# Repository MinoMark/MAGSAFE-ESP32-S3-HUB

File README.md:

# MAGSAFE ESP32-S3 HUB
**Don't get up, just use this...**

## About My Project

What is my project? My project is one of a kind! I am using an ESP32-S3 microcontroller chip to power a smart 2.8" TFT touchscreen. As mentioned in the title, it is listed as being MagSafe compatible, which is ingenious, right? Who does not want to have it charging 24/7? Or maybe not? Well, that has been solved too! I have added a 3.7V 5000mAh LiPo battery that can last well over 24 hours. But that is not all! I have also included an audio amplifier with a super loud and crisp speaker so you can hear those alerts and alarms from meters away.

I’ve made this project because I am tired of opening my laptop just to have a look at the time, set a timer, turn on smart lights, or do almost anything else. With my design, I’ll be able to control these all in one. You can have it play soothing music or play annoying alarms whenever.

**How to use:**

Plug it into the dedicated USB-C port at the bottom side with a USB-C cable or any compatible iPhone MagSafe charger. Let it charge for 10 minutes to an hour to fully charge. For MagSafe, let it charge for 30 minutes to an hour and 15 minutes.

**Wiring Diagram:**

The wiring diagram for POWER:

The wiring diagram for AUDIO:

## Schematics
The schematics of my final design, what I'll be using to make the main PCB.

## PCB
The fully routed PCB, with fun easter egg and smart eletrical wiring choices that save money and change the path of electricity more efficiently.

## CAD
A full design of the parts.

## BOM

# Bill of Materials

| Part | Type | Quantity | Unit price (USD) | Line total (USD) | Link | Vendor | Funding | Notes | Reference | Footprint | Datasheet | MPN | LCSC |
|---|---|---|---|---|---|---|---|---|---|---|---|---|---|
| Shipping (JLCONE) | Shipping | 1 | 12.51 | 12.51 | [Link](<https://jlcpcb.com/?from=VGS&utm_source=google&utm_medium=cpc&utm_campaign=14177189905&gad_source=1&gad_campaignid=14177189905&gbraid=0AAAAABS1QqkgPoFOHUy_26J4N5kBx4Aa3&gclid=Cj0KCQiAwdDXBhDuARIsAFdLukmN-B7r3FdQKI8Ma6WjcPEJgnZSJuI_80tu4TU9jCkDFhZ-cYRUD3oaAn0kEALw_wcB>) | JLCPCB | Grant |  | N/A | N/A | N/A | N/A | N/A |
| Shipping (AliExpress) | Shipping | 1 | 2.03 | 2.03 | N/A | AliExpress | Grant |  | N/A | N/A | N/A | N/A | N/A |
| Tax (AliExpress) | Tax or fee | 1 | 1.74 | 1.74 | N/A | AliExpress | Grant |  | N/A | N/A | N/A | N/A | N/A |
| MAX98357A audio amplifier | Part | 1 | 2.07 | 2.07 | [Link](<https://www.aliexpress.com/item/1005007003802663.html?spm=a2g0o.productlist.main.4.2bd23ce0doG6x8&aem_p4p_detail=202611050133081315319932123740002772996&algo_pvid=0ad6be40-46e3-4f00-9430-e9820924795f&algo_exp_id=0ad6be40-46e3-4f00-9430-e9820924795f-3&pdp_ext_f=%7B%22order%22%3A%223834%22%2C%22spu_best_type%22%3A%22price%22%2C%22eval%22%3A%221%22%2C%22fromPage%22%3A%22search%22%7D&pdp_npi=6%40dis%21AUD%212.99%212.84%21%21%2113.80%2113.11%21%402101ca9517938711880116699e0d41%2112000052658790894%21sea%21AU%212961347876%21X%211%210%21n_tag%3A-29919%3Bd%3A20f6a0d2%3Bm03_new_user%3A-29895%3BpisId%3A5000000220905999&curPageLogUid=gHNWoxg3Cup0&utparam-url=scene%3Asearch%7Cquery_from%3A%7Cx_object_id%3A1005007003802663%7C_p_origin_prod%3A&search_p4p_id=202611050133081315319932123740002772996_1>) | AliExpress | Grant |  | MAX98357A | N/A | [Datasheet](<https://www.analog.com/media/en/technical-documentation/data-sheets/MAX98357A-MAX98357B.pdf>) | N/A | N/A |
| Wireless charger receiver | Part | 1 | 2.92 | 2.92 | [Link](<https://www.aliexpress.com/item/1005006917890401.html?spm=a2g0o.productlist.main.21.5befc5e30wHdxF&algo_pvid=c3f727d4-7764-4de2-9cfe-4073aea75173&algo_exp_id=c3f727d4-7764-4de2-9cfe-4073aea75173-18&pdp_ext_f=%7B%22order%22%3A%22260%22%2C%22spu_best_type%22%3A%22price%22%2C%22eval%22%3A%221%22%2C%22fromPage%22%3A%22search%22%7D&pdp_npi=6%40dis%21AUD%213.98%213.49%21%21%212.75%212.41%21%402101d2e717938715347906588e0f1b%2112000038722150536%21sea%21AU%212961347876%21X%211%210%21n_tag%3A-29919%3Bd%3A20f6a0d2%3Bm03_new_user%3A-29895%3BpisId%3A5000000220770329&curPageLogUid=ptJgFovmIGzU&utparam-url=scene%3Asearch%7Cquery_from%3A%7Cx_object_id%3A1005006917890401%7C_p_origin_prod%3A>) | AliExpress | Grant |  | 5W | N/A | N/A | N/A | N/A |
| Battery management board | Part | 1 | 0.80 | 0.80 | [Link](<https://www.aliexpress.com/item/1005013472412754.html?spm=a2g0o.productlist.main.9.7fb4e999hY7Rre&algo_pvid=98fe2f10-0cd6-416a-bbd2-9b577de21ebe&algo_exp_id=98fe2f10-0cd6-416a-bbd2-9b577de21ebe-8&pdp_ext_f=%7B%22order%22%3A%225%22%2C%22spu_best_type%22%3A%22price%22%2C%22eval%22%3A%221%22%2C%22fromPage%22%3A%22search%22%7D&pdp_npi=6%40dis%21AUD%212.45%210.97%21%21%2111.31%214.51%21%402101d33417938729376868658e0dc7%2112000061234386246%21sea%21AU%212961347876%21X%211%210%21n_tag%3A-29919%3Bd%3A20f6a0d2%3Bm03_new_user%3A-29895%3BpisId%3A5000000220868114&curPageLogUid=SZ1nXcZwQJOj&utparam-url=scene%3Asearch%7Cquery_from%3A%7Cx_object_id%3A1005013472412754%7C_p_origin_prod%3A>) | AliExpress | Grant |  | 1X-Type C | N/A | N/A | N/A | N/A |
| 5000mAh 955565 Lipo Lithium Battery | Part | 1 | 8.55 | 8.55 | [Link](<https://www.aliexpress.com/item/1005012710344008.html?spm=a2g0o.detail.0.0.4f13zLNrzLNrYC&mp=1&pdp_npi=6%40dis%21AUD%21AUD+44.89%21AUD+12.70%21%21AUD+12.70%21%21%21%402101c69517948801902018396e0e59%2112000059134254104%21ct%21AU%212961347876%21%211%210%21>) | AliExpress | Grant |  | 3.7 V | N/A | N/A | N/A | N/A |
| 2W Speaker | Part | 1 | 2.60 | 2.60 | [Link](<https://www.aliexpress.com/item/1005007640238935.html?spm=a2g0o.detail.pcDetailTopMoreOtherSeller.4.6cacshuCshuCnA&gps-id=pcDetailTopMoreOtherSeller&scm=1007.40050.354490.0&scm_id=1007.40050.354490.0&scm-url=1007.40050.354490.0&pvid=b61e8163-83fe-4c95-9dc5-7b9f26661546&_t=gps-id%3ApcDetailTopMoreOtherSeller%2Cscm-url%3A1007.40050.354490.0%2Cpvid%3Ab61e8163-83fe-4c95-9dc5-7b9f26661546%2Ctpp_buckets%3A668%232846%238110%231995&pdp_ext_f=%7B%22order%22%3A%222631%22%2C%22eval%22%3A%221%22%2C%22sceneId%22%3A%2230050%22%2C%22fromPage%22%3A%22recommend%22%7D&pdp_npi=6%40dis%21AUD%214.06%213.69%21%21%2118.49%2116.82%21%402103117b17940474651706506e0d0b%2112000041608234950%21rec%21AU%212961347876%21XZ%211%210%21n_tag%3A-29919%3Bd%3A20f6a0d2%3Bm03_new_user%3A-29895%3BpisId%3A5000000220905999&utparam-url=scene%3ApcDetailTopMoreOtherSeller%7Cquery_from%3A%7Cx_object_id%3A1005007640238935%7C_p_origin_prod%3A>) | AliExpress | Grant |  | 2535 4 ohm 3W | N/A | N/A | N/A | N/A |
| 2.8" TFT Screen | Part | 1 | 7.60 | 7.60 | [Link](<https://www.aliexpress.com/item/1005008568072063.html?spm=a2g0o.productlist.main.11.1c26482dWSHE9j&algo_pvid=15dab31f-5e3b-4a75-826a-e8b2a567e931&algo_exp_id=15dab31f-5e3b-4a75-826a-e8b2a567e931-10&pdp_ext_f=%7B%22order%22%3A%22174%22%2C%22eval%22%3A%221%22%2C%22fromPage%22%3A%22search%22%7D&pdp_npi=6%40dis%21AUD%2115.38%216.34%21%21%2168.37%2128.16%21%402101c69517948838882406752e0f63%2112000045752604980%21sea%21AU%212961347876%21X%211%210%21n_tag%3A-29919%3Bd%3A20f6a0d2%3Bm03_new_user%3A-29895%3BpisId%3A5000000221713830&curPageLogUid=v0UEPRpnLVGD&utparam-url=scene%3Asearch%7Cquery_from%3A%7Cx_object_id%3A1005008568072063%7C_p_origin_prod%3A>) | AliExpress | Already own |  | 2.8 Inch Display | N/A | N/A | N/A | N/A |
| Shipping (LCSC) | Shipping | 1 | 1.53 | 1.53 | [Link](<https://www.lcsc.com/cart?spm=wm.sy.ssl.gwc&lcsc_vid=Q1NWAwBXFFVfAVUFQgcLBgFQEwdYA1QAQgdWAgZeFAIxVlNfQlFdX1JRRVlbUzsOAxUeFF5JWBEPFBcWGBMaSQgFBAJABAsLWA%3D%3D>) | LCSC | Grant |  | N/A | N/A | N/A | N/A | N/A |
| 0Ω resistor | Part | 100 | 0.0012 | 0.12 | [Link](<https://www.lcsc.com/product-detail/C17168.html>) | LCSC | Grant | UNI-ROYAL – 0Ω ±1% 62.5mW 0402 Thick Film Resistor | N/A | 0402 | [Datasheet](<https://www.lcsc.com/datasheet/C17168.pdf>) | 0402WGF0000TCE | C17168 |
| 32.768kHz crystal | Part | 5 | 0.6128 | 3.06 | [Link](<https://www.lcsc.com/product-detail/C1985240.html>) | LCSC | Grant | ABRACON – Crystal 32.768kHz ±20ppm 6pF 55kΩ SMD3215-2P | N/A | SMD3215-2P | [Datasheet](<https://www.lcsc.com/datasheet/C1985240.pdf>) | ABS07-120-32.768KHZ-T | C1985240 |
| ESP32-S3-WROOM-1-N16R8 module | Part | 5 | 5.3999 | 27.00 | [Link](<https://www.lcsc.com/product-detail/C2913202.html>) | LCSC | Grant | ESPRESSIF – 2.4GHz ESP32-S3R8 On-board PCB Antenna -103.5dBm SMD,25.5x18mm RF Transceiver Modules and Modems RoHS | N/A | SMD,25.5x18mm | [Datasheet](<https://www.lcsc.com/datasheet/C2913202.pdf>) | ESP32-S3-WROOM-1-N16R8 | C2913202 |
| USBLC6-2P6 USB ESD protection | Part | 5 | 0.1572 | 0.79 | [Link](<https://www.lcsc.com/product-detail/C2827693.html>) | LCSC | Grant | TECH PUBLIC – 14VC Clamp 5.5A Ipp ESD DIODE SOT-666-6 | N/A | SOT-666-6 | [Datasheet](<https://www.lcsc.com/datasheet/C2827693.pdf>) | USBLC6-2P6 | C2827693 |
| AP2112K-3.3 LDO regulator | Part | 10 | 0.1683 | 1.68 | [Link](<https://www.lcsc.com/product-detail/C51118.html>) | LCSC | Grant | DIODES – 3.3V Positive Fixed SOT-25-5 Voltage Regulators - Linear, Low Drop Out (LDO) Regulators RoHS | N/A | SOT-25-5 | [Datasheet](<https://www.lcsc.com/datasheet/C51118.pdf>) | AP2112K-3.3TRG1 | C51118 |
| Tactile switch | Part | 10 | 0.0415 | 0.42 | [Link](<https://www.lcsc.com/product-detail/C255802.html>) | LCSC | Grant | HYP – Tactile Switch SPST 250gf 2.5mm Gull Wing 6.1mm x 3.7mm Surface Mount | N/A | SMD,6x3.7mm | [Datasheet](<https://www.lcsc.com/datasheet/C255802.pdf>) | 1TS002E-2500-2501-CT | C255802 |
| 22Ω resistor (5%) | Part | 100 | 0.0017 | 0.17 | [Link](<https://www.lcsc.com/product-detail/C25152.html>) | LCSC | Grant | UNI-ROYAL – 22Ω ±5% 62.5mW 0402 Thick Film Resistor | N/A | 0402 | [Datasheet](<https://www.lcsc.com/datasheet/C25152.pdf>) | 0402WGJ0220TCE | C25152 |
| 1kΩ resistor | Part | 100 | 0.0013 | 0.13 | [Link](<https://www.lcsc.com/product-detail/C11702.html>) | LCSC | Grant | UNI-ROYAL – 1kΩ ±1% 62.5mW 0402 Thick Film Resistor | N/A | 0402 | [Datasheet](<https://www.lcsc.com/datasheet/C11702.pdf>) | 0402WGF1001TCE | C11702 |
| 5.1kΩ resistor | Part | 100 | 0.0014 | 0.14 | [Link](<https://www.lcsc.com/product-detail/C25905.html>) | LCSC | Grant | UNI-ROYAL – 5.1kΩ ±1% 62.5mW 0402 Thick Film Resistor | N/A | 0402 | [Datasheet](<https://www.lcsc.com/datasheet/C25905.pdf>) | 0402WGF5101TCE | C25905 |
| 22Ω resistor (1%) | Part | 100 | 0.001 | 0.10 | [Link](<https://www.lcsc.com/product-detail/C25092.html>) | LCSC | Grant | UNI-ROYAL – 22Ω ±1% 62.5mW 0402 Thick Film Resistor | N/A | 0402 | [Datasheet](<https://www.lcsc.com/datasheet/C25092.pdf>) | 0402WGF220JTCE | C25092 |
| 10kΩ resistor | Part | 100 | 0.0016 | 0.16 | [Link](<https://www.lcsc.com/product-detail/C2765610.html>) | LCSC | Grant | UNI-ROYAL – 10kΩ ±1% 62.5mW 0402 Thick Film Resistor AEC-Q200 | N/A | 0402 | [Datasheet](<https://www.lcsc.com/datasheet/C2765610.pdf>) | CQ02WGF1002TCE | C2765610 |
| 100nF capacitor | Part | 200 | 0.0024 | 0.48 | [Link](<https://www.lcsc.com/product-detail/C1525.html>) | LCSC | Grant | Samsung Electro-Mechanics – 100nF ±10% 16V Ceramic Capacitor X7R 0402 | N/A | 0402 | [Datasheet](<https://www.lcsc.com/datasheet/C1525.pdf>) | CL05B104KO5NNNC | C1525 |
| UMH3N dual transistor | Part | 10 | 0.0503 | 0.50 | [Link](<https://www.lcsc.com/product-detail/C62892.html>) | LCSC | Grant | JSCJ – Pre-Biased Bipolar Transistor (BJT) 50V 100mA 150mW Surface Mount SOT-363 | N/A | SOT-363 | [Datasheet](<https://www.lcsc.com/datasheet/C62892.pdf>) | UMH3N | C62892 |
| USB-C receptacle | Part | 10 | 0.1737 | 1.74 | [Link](<https://www.lcsc.com/product-detail/C165948.html>) | LCSC | Grant | Korean Hroparts Elec – USB-C (USB TYPE-C) Receptacle Connector 16 Position Surface Mount | N/A | SMD | [Datasheet](<https://www.lcsc.com/datasheet/C165948.pdf>) | TYPE-C-31-M-12 | C165948 |
| ESD5Z3.3 TVS diode | Part | 10 | 0.038 | 0.38 | [Link](<https://www.lcsc.com/product-detail/C61148.html>) | LCSC | Grant | onsemi – 14.1VC Clamp 11.2A Ipp TVS DIODE SOD-523 | N/A | SOD-523 | [Datasheet](<https://www.lcsc.com/datasheet/C61148.pdf>) | ESD5Z3.3T1G | C61148 |
| Red LED | Part | 100 | 0.0036 | 0.36 | [Link](<https://www.lcsc.com/product-detail/C965799.html>) | LCSC | Grant | XINGLIGHT – Red 625nm LED Indication - Discrete 2.3V 0603 | N/A | 0603 | [Datasheet](<https://www.lcsc.com/datasheet/C965799.pdf>) | XL-1608SURC-06 | C965799 |
| SS34 Schottky diode | Part | 20 | 0.0354 | 0.71 | [Link](<https://www.lcsc.com/product-detail/C8678.html>) | LCSC | Grant | MDD(Microdiode Semiconductor) – Diode Independent 40V 3A Surface Mount SMA(DO-214AC) | N/A | SMA(DO-214AC) | [Datasheet](<https://www.lcsc.com/datasheet/C8678.pdf>) | SS34 | C8678 |
| 6.8pF capacitor | Part | 100 | 0.0023 | 0.23 | [Link](<https://www.lcsc.com/product-detail/C1576.html>) | LCSC | Grant | FH – 6.8pF 50V Ceramic Capacitor C0G 0402 | N/A | 0402 | [Datasheet](<https://www.lcsc.com/datasheet/C1576.pdf>) | 0402CG6R8C500NT | C1576 |
| 22uF capacitor | Part | 20 | 0.1094 | 2.19 | [Link](<https://www.lcsc.com/product-detail/C45783.html>) | LCSC | Grant | Samsung Electro-Mechanics – 22uF ±20% 25V Ceramic Capacitor X5R 0805 | N/A | 0805 | [Datasheet](<https://www.lcsc.com/datasheet/C45783.pdf>) | CL21A226MAQNNNE | C45783 |
| 1uF capacitor | Part | 100 | 0.0056 | 0.56 | [Link](<https://www.lcsc.com/product-detail/C52923.html>) | LCSC | Grant | Samsung Electro-Mechanics – 1uF ±10% 25V Ceramic Capacitor X5R 0402 | N/A | 0402 | [Datasheet](<https://www.lcsc.com/datasheet/C52923.pdf>) | CL05A105KA5NQNC | C52923 |
| 10uF capacitor | Part | 20 | 0.0561 | 1.12 | [Link](<https://www.lcsc.com/product-detail/C2846677.html>) | LCSC | Grant | FH – 10uF ±20% 10V Ceramic Capacitor X5R 0402 | N/A | 0402 | [Datasheet](<https://www.lcsc.com/datasheet/C2846677.pdf>) | 0402X106M100NT | C2846677 |
| PCB (JLCONE) | Part | 10 | 0.50 | 5.00 | N/A | JLCPCB | Grant |  | N/A | N/A | N/A | N/A | N/A |
| SMT Stencil | Part | 1 | 7.18 | 7.18 | N/A | JLCPCB | Grant |  | N/A | N/A | N/A | N/A | N/A |
| Romeda Rosin Soldering Flux Paste, 2 x 35 g Jars | Part | 1 | 4.50 | 4.50 | [Link](<https://www.amazon.com.au/Romeda-Soldering-Colour-boxed-electronics-compatible/dp/B08MVXW4RY/ref=sr_1_14_so_TOOLS?crid=1D428T4PT5BOL&dib=eyJ2IjoiMSJ9.vxYBNyOz7ezkrOjlIjU_0mtrJuUNQ3_-BtulHOAmH4rstA2iFWs1P9ByIw9TC8YLI1447o_luWe3T7nH_mo0p9N-Jazd8OnW7x8AN69IPk5F5T9noG1LPlYMo80e_2HOxYpyTH8KwyKAfuy42aWzNTR9tKZGHimXOUgbS8074EVtkGc7dStC64PInYo9a2C41aMEurn6YsAf7uIKpN0KoUsPk672iNgQUNMUWCV5zCo.wCZo25IfjjDzIHOHOIbSZ3mes82VXEAVgn1mLPuGwKg&dib_tag=se&keywords=solder+paste&qid=1795259228&s=home-improvement&sprefix=solder+past%2Chome-improvement%2C226&sr=1-14>) | Amazon | Grant | Card is in AUD, I changed to USD in the BOM price | N/A | N/A | N/A | N/A | N/A |
| Solder Paste | Part | 1 | 17.00 | 17.00 | [Link](<https://www.amazon.com.au/Wonderway-Soldering-Electronics-CELLPHONE-Repairing/dp/B0BLSJQPR6/ref=sr_1_16?crid=1D428T4PT5BOL&dib=eyJ2IjoiMSJ9.vxYBNyOz7ezkrOjlIjU_0mtrJuUNQ3_-BtulHOAmH4rstA2iFWs1P9ByIw9TC8YLI1447o_luWe3T7nH_mo0p9N-Jazd8OnW7x8AN69IPk5F5T9noG1LPlYMo80e_2HOxYpyTH8KwyKAfuy42aWzNTR9tKZGHimXOUgbS8074EVtkGc7dStC64PInYo9a2C41aMEurn6YsAf7uIKpN0KoUsPk672iNgQUNMUWCV5zCo.wCZo25IfjjDzIHOHOIbSZ3mes82VXEAVgn1mLPuGwKg&dib_tag=se&keywords=solder%2Bpaste&qid=1795259228&s=home-improvement&sprefix=solder%2Bpast%2Chome-improvement%2C226&sr=1-16&th=1>) | Amazon | Grant | Card is in AUD, I changed to USD in the BOM price | N/A | N/A | N/A | N/A | N/A |

**Total:** $118.07 USD  
**Grant total:** $110.47 USD

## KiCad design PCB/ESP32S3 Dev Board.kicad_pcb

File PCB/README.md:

# All My Schematics and PCB Designs

**About My Design**

I have used many different things in my schematic I have never used before with some of these actually helping and others for convenience.

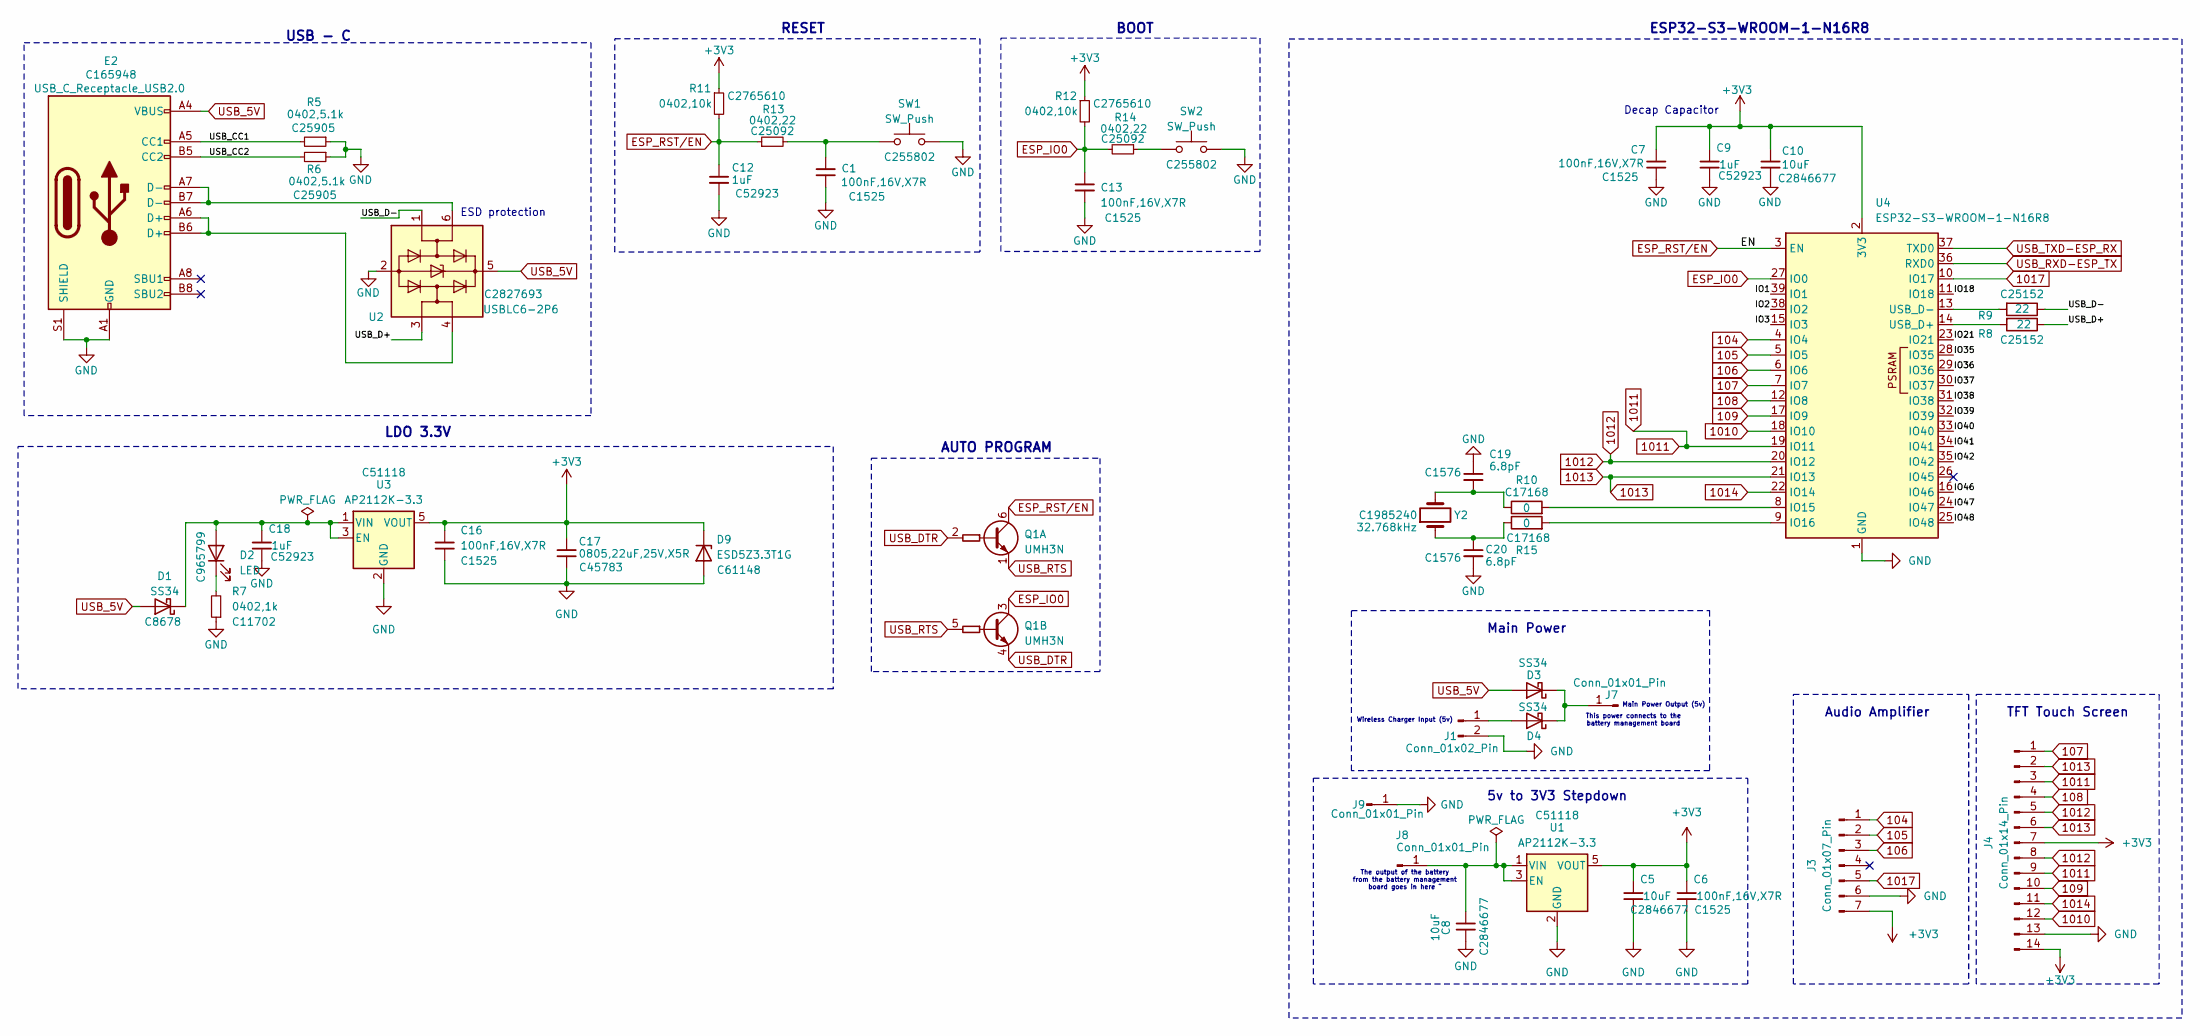
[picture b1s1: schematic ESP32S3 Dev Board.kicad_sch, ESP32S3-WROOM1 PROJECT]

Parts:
C1, C6, C7, C13, C16: 100nF,16V,X7R; C_0402_1005Metric; MFGPN CL05B104KO5NNNC; LCSC C1525
C5, C8, C10: 10uF; C_0402_1005Metric; MFGPN 0402X106M100NT; LCSC C2846677
C9, C12, C18: 1uF; C_0402_1005Metric; MFGPN CL05A105KA5NQNC; LCSC C52923
C17: 0805,22uF,25V,X5R; C_0805_2012Metric; MFGPN CL21A226MAQNNNE; LCSC C45783
C19, C20: 6.8pF; C_0402_1005Metric; MFGPN 0402CG6R8C500NT; LCSC C1576
D1, D3, D4: SS34; D_SMA; MFGPN SS34; LCSC C8678
D2: LED; LED_0603_1608Metric; MPN XL-1608SURC-06; LCSC C965799
D9: ESD5Z3.3T1G; D_SOD-523; MFGPN ESD5Z3.3T1G; LCSC C61148
E2: USB_C_Receptacle_USB2.0; USB_C_Receptacle_HRO_TYPE-C-31-M-12; MFGPN TYPE-C-31-M-12; LCSC C165948
J1: Conn_01x02_Pin; PinHeader_1x02_P2.54mm_Vertical; MFGPN PZ254V-11-02P; LCSC C492401
J3: Conn_01x07_Pin; PinHeader_1x07_P2.54mm_Vertical; MFGPN PZ254V-11-07P; LCSC C492406
J4: Conn_01x14_Pin; PinHeader_1x14_P2.54mm_Vertical; MFGPN PZ254V-11-14P; LCSC C22465874
J7, J8, J9: Conn_01x01_Pin; SolderWirePad_1x01_SMD_1.5x3mm; MFGPN N/A; LCSC N/A
Q1: UMH3N; SOT-363_SC-70-6; MFGPN UMH3N; LCSC C62892
R5, R6: 0402,5.1k; R_0402_1005Metric; MFGPN 0402WGF5101TCE; LCSC C25905
R7: 0402,1k; R_0402_1005Metric; MFGPN 0402WGF1001TCE; LCSC C11702
R8, R9: 22; R_0402_1005Metric; MFGPN 0402WGJ0220TCE; LCSC C25152
R10, R15: 0; R_0402_1005Metric; MFGPN 0402WGF0000TCE; LCSC C17168
R11, R12: 0402,10k; R_0402_1005Metric; MFGPN CQ02WGF1002TCE; LCSC C2765610
R13, R14: 0402,22; R_0402_1005Metric; MFGPN 0402WGF220JTCE; LCSC C25092
SW1, SW2: SW_Push; SW_SPST_CK_RS282G05A3; MFGPN 1TS002E-2500-2501-CT; LCSC C255802
U1, U3: AP2112K-3.3; SOT-23-5; MFGPN AP2112K-3.3TRG1; LCSC C51118
U2: USBLC6-2P6; SOT-666; MFGPN USBLC6-2P6; LCSC C2827693
U4: ESP32-S3-WROOM-1-N16R8; ESP32-S3-WROOM-1; MFGPN ESP32-S3-WROOM-1-N16R8; LCSC C2913202
Y2: 32.768kHz; Crystal_SMD_3215-2Pin_3.2x1.5mm; MFGPN ABS07-120-32.768KHZ-T; LCSC C1985240

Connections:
104: J3.1, U4.4 (IO4)
105: J3.2, U4.5 (IO5)
106: J3.3, U4.6 (IO6)
107: J4.1, U4.7 (IO7)
108: J4.4, U4.12 (IO8)
109: J4.10, U4.17 (IO9)
1010: J4.12, U4.18 (IO10)
1011: J4.3, J4.9, U4.19 (IO11)
1012: J4.5, J4.8, U4.20 (IO12)
1013: J4.2, J4.6, U4.21 (IO13)
1014: J4.11, U4.22 (IO14)
1017: J3.5, U4.10 (IO17)
+3V3: C5.1, C6.1, C7.1, C9.1, C10.1, C16.1, C17.1, D9.1 (K), J3.7, J4.7, J4.14, R11.1, R12.1, U1.5 (VOUT), U3.5 (VOUT), U4.2 (3V3)
/IO1: U4.39 (IO1)
/IO2: U4.38 (IO2)
/IO3: U4.15 (IO3)
/IO18: U4.11 (IO18)
/IO21: U4.23 (IO21)
/IO35: U4.28 (IO35)
/IO36: U4.29 (IO36)
/IO37: U4.30 (IO37)
/IO38: U4.31 (IO38)
/IO39: U4.32 (IO39)
/IO40: U4.33 (IO40)
/IO41: U4.34 (IO41)
/IO42: U4.35 (IO42)
/IO46: U4.16 (IO46)
/IO47: U4.24 (IO47)
/IO48: U4.25 (IO48)
/USB_CC1: E2.A5 (CC1), R5.2
/USB_CC2: E2.B5 (CC2), R6.2
/USB_D+: R8.1, U2.3 (I/O2)
/USB_D-: R9.1, U2.1 (I/O1)
ESP_IO0: C13.1, Q1.3 (C2), R12.2, R14.2, U4.27 (IO0)
ESP_RST/EN: C12.1, Q1.6 (C1), R11.2, R13.1, U4.3 (EN)
GND: C1.2, C5.2, C6.2, C7.2, C8.1, C9.2, C10.2, C12.2, C13.2, C16.2, C17.2, C18.2, C19.1, C20.2, D9.2 (A), E2.A1 (GND), E2.A12 (GND), E2.B1 (GND), E2.B12 (GND), E2.S1 (SHIELD), J1.2, J3.6, J4.13, J9.1 (Pin_1_1), R5.1, R6.1, R7.1, SW1.2, SW2.2, U1.2 (GND), U2.2 (GND), U3.2 (GND), U4.1 (GND), U4.40 (GND), U4.41 (GND)
unnamed: C1.1, R13.2, SW1.1
unnamed: C19.2, R10.1, Y2.2
unnamed: C20.1, R15.1, Y2.1
unnamed: C18.1, D1.1 (K), D2.2 (A), U3.1 (VIN), U3.3 (EN)
unnamed: D2.1 (K), R7.2
unnamed: D3.1 (K), D4.1 (K), J7.1 (Pin_1_1)
unnamed: D4.2 (A), J1.1
unnamed: E2.A6 (D+), E2.B6 (D+), U2.4 (I/O2)
unnamed: E2.A7 (D-), E2.B7 (D-), U2.6 (I/O1)
unnamed: C8.2, J8.1 (Pin_1_1), U1.1 (VIN), U1.3 (EN)
unnamed: R14.1, SW2.1
unnamed: R10.2, U4.8 (IO15)
unnamed: R15.2, U4.9 (IO16)
unnamed: R8.2, U4.14 (USB_D+)
unnamed: R9.2, U4.13 (USB_D-)
USB_5V: D1.2 (A), D3.2 (A), E2.A4 (VBUS), E2.A9 (VBUS), E2.B4 (VBUS), E2.B9 (VBUS), U2.5 (VBUS)
USB_DTR: Q1.2 (B1), Q1.4 (E2)
USB_RTS: Q1.1 (E1), Q1.5 (B2)
USB_RXD-ESP_TX: U4.36 (RXD0)
USB_TXD-ESP_RX: U4.37 (TXD0)

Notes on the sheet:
TFT Touch Screen
BOOT
LDO 3.3V
The output of the battery from the battery management board goes in here ^
USB - C
ESD protection
RESET
Decap Capacitor
5v to 3V3 Stepdown
Main Power Output (5v)
Main Power
This power connects to the battery management board
Audio Amplifier
Wireless Charger Input (5v)
ESP32-S3-WROOM-1-N16R8
AUTO PROGRAM

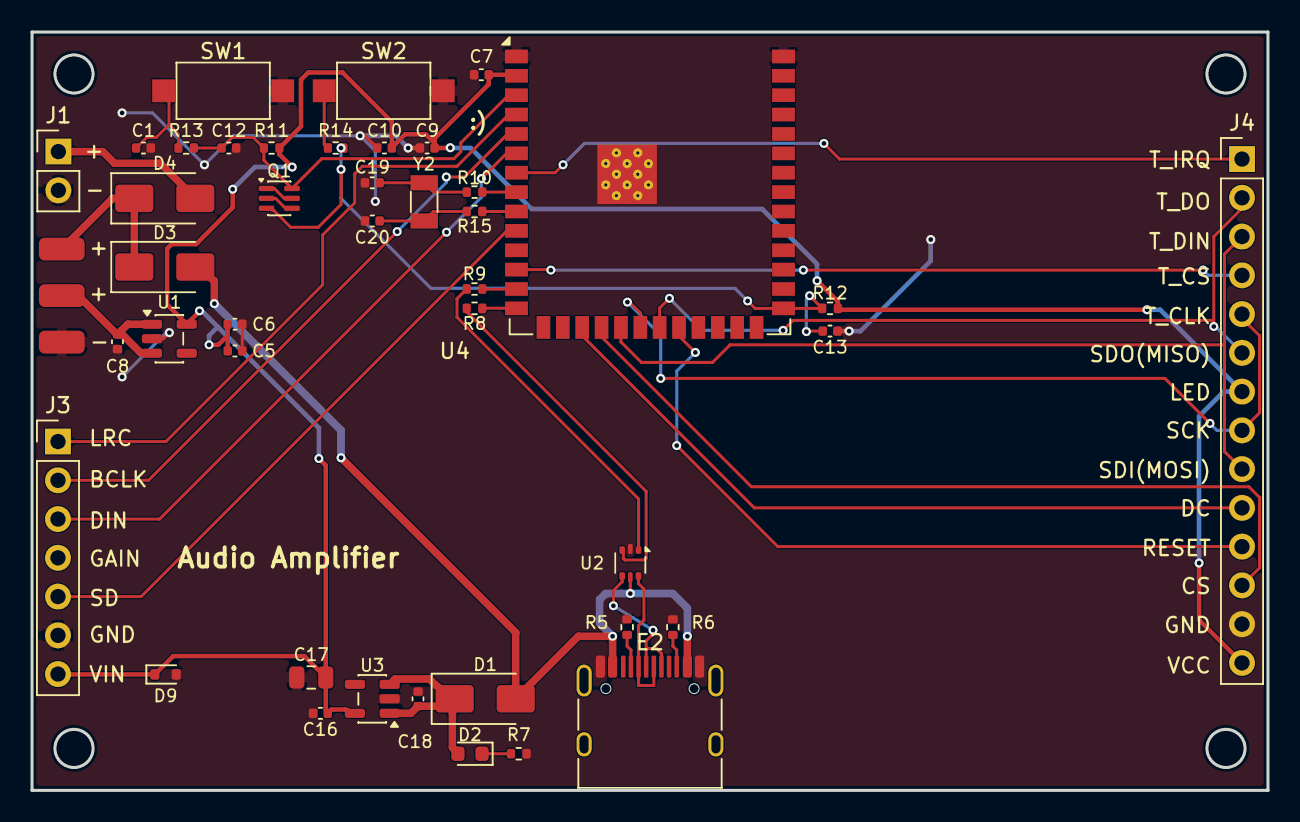
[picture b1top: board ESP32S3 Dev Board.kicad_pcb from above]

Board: 2 copper layers, 81.0 x 49.7 mm, 45 parts (0 on the bottom side), 38 nets.

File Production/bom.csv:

Designator,Footprint,Quantity,Value,LCSC Part #
"C1, C16, C7",0402,3,"100nF,16V,X7R",C1525
"C10, C5, C8",0402,3,10uF,C2846677
"C12, C18, C9",0402,3,1uF,C52923
"C13, C6",0402,2,100nF,C1525
C17,0805,1,"0805,22uF,25V,X5R",C45783
"C19, C20",0402,2,6.8pF,C1576
"D1, D3, D4",D_SMA,3,SS34,C8678
D2,0603,1,LED,C965799
D9,D_SOD-523,1,ESD5Z3.3T1G,C61148
E2,USB_C_Receptacle_HRO_TYPE-C-31-M-12,1,USB_C_Receptacle_USB2.0,C165948
J1,PinHeader_1x02_P2.54mm_Vertical,1,Conn_01x02_Pin,C492401
J3,PinHeader_1x07_P2.54mm_Vertical,1,Conn_01x07_Pin,C492406
J4,PinHeader_1x14_P2.54mm_Vertical,1,Conn_01x14_Pin,C22465874
"J7, J8, J9",SolderWirePad_1x01_SMD_1.5x3mm,3,Conn_01x01_Pin,N/A
Q1,SOT-363_SC-70-6,1,UMH3N,C62892
"R10, R15",0402,2,0,C17168
"R11, R12",0402,2,"0402,10k",C2765610
"R13, R14",0402,2,"0402,22",C25092
"R5, R6",0402,2,"0402,5.1k",C25905
R7,0402,1,"0402,1k",C11702
"R8, R9",0402,2,22,C25152
"SW1, SW2",SW_SPST_CK_RS282G05A3,2,SW_Push,C255802
"U1, U3",SOT-23-5,2,AP2112K-3.3,C51118
U2,SOT-666,1,USBLC6-2P6,C2827693
U4,ESP32-S3-WROOM-1,1,ESP32-S3-WROOM-1-N16R8,C2913202
Y2,Crystal_SMD_3215-2Pin_3.2x1.5mm,1,32.768kHz,C1985240
